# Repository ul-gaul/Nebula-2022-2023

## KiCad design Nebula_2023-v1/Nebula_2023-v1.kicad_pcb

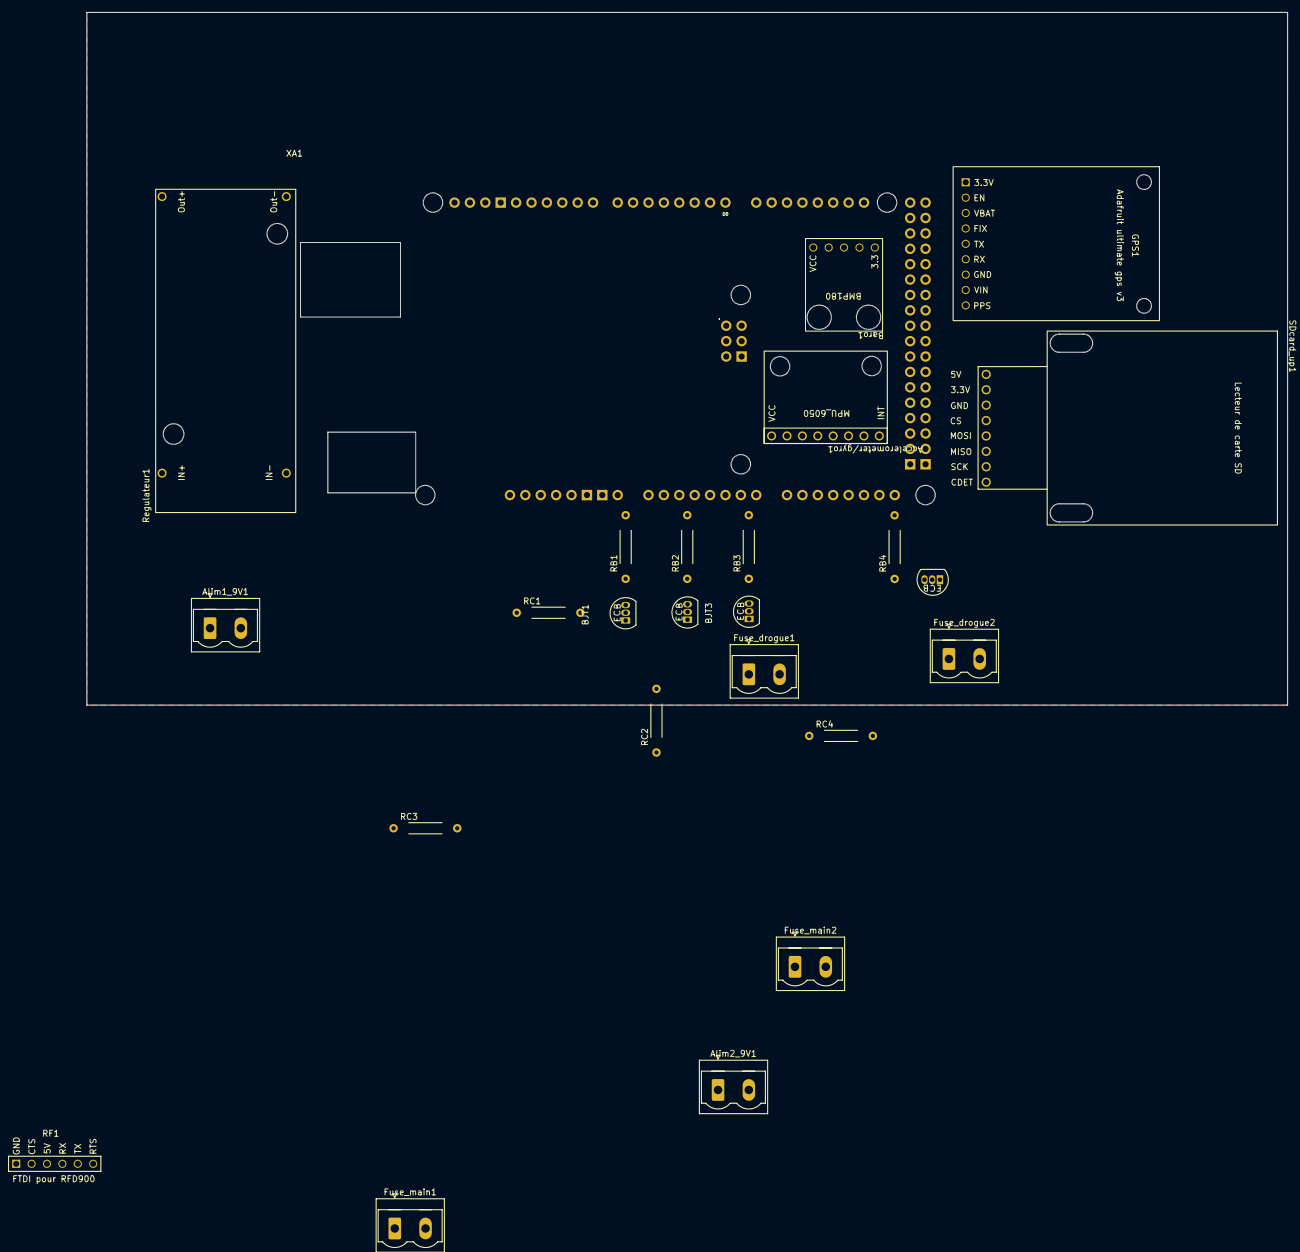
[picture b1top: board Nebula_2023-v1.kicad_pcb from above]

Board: 2 copper layers, 198.1 x 114.3 mm, 25 parts (0 on the bottom side), 34 nets, no tracks yet.

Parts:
Accelerometer/gyro1: MPU6050_6DOF_GY-521; MPU_6050
Alim1_9V1, Alim2_9V1: Screw_Terminal_KF301-2P; MKDSN_1729128_PCB terminal block
BJT1, BJT2, BJT3, BJT4: 2SC3279
Baro1: BMP18; BMP
Fuse_drogue1, Fuse_drogue2: Screw_Terminal_KF301-2P; MKDSN_1729128_PCB terminal block
Fuse_main1, Fuse_main2: Screw_Terminal_KF301-2P; MKDSN_1729128_PCB terminal block
GPS1: Adafruit_ultimate_gps_V3; Adafruit_GPS_V3
RB1, RB2, RB3, RB4: Resistance; Resistance through-hole
RC1, RC2, RC3, RC4: Resistance; Resistance through-hole
RF1: RFD900; RFD900_externe
Regulateur1: Voltage_regulator; Regulateur_voltage
SDcard_up1: Module_GPS_Robotdyn; SD Card Reader
XA1: Arduino_Mega2560_Shield; Arduino_mega_custom_shield_open

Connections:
/A1: RB1.2, XA1.A1
/A2: RB2.2, XA1.A2
/A3: RB3.2, XA1.A3
/A4: RB4.2, XA1.A4
/D2: Accelerometer/gyro1.8 (INT), XA1.D2 (D2_INT0)
/D23: GPS1.4 (FIX), XA1.D23
/D25: GPS1.9 (PPS), XA1.D25
/D50: SDcard_up1.6 (MISO), XA1.D50 (D50_MISO)
/D51: SDcard_up1.5 (MOSI), XA1.D51 (D51_MOSI)
/D52: SDcard_up1.7 (SCK), XA1.D52 (D52_SCK)
/D53: SDcard_up1.4 (CS), XA1.D53 (D53_CS)
/RX0: RF1.5 (TX), XA1.D0 (D0/RX0)
/RX1: GPS1.5 (TX), XA1.D19 (D19/RX1)
/SCL: Accelerometer/gyro1.3 (SCL), Baro1.3 (SCL), XA1.D21 (D21/SCL)
/SDA: Accelerometer/gyro1.4 (SDA), Baro1.4 (SDA), XA1.D20 (D20/SDA)
/TX0: RF1.4 (RX), XA1.D1 (D1/TX0)
/TX1: GPS1.6 (RX), XA1.D18 (D18/TX1)
/VBat1: Alim1_9V1.1 (V+), RC1.1, RC3.1, XA1.VIN
/VBat2: Alim2_9V1.1 (V+), RC2.1, RC4.1, Regulateur1.1 (IN+)
/VCC: Accelerometer/gyro1.1 (VCC), Baro1.1 (VCC), GPS1.8 (VIN), SDcard_up1.1 (5V), XA1.5V1 (5V)
/VREG_5V: RF1.3 (VCC), Regulateur1.3 (OUT+)
GND: Accelerometer/gyro1.2 (GND), Alim1_9V1.2 (V-), Alim2_9V1.2 (V-), Baro1.2 (GND), Fuse_drogue1.2 (V-), Fuse_drogue2.2 (V-), Fuse_main1.2 (V-), Fuse_main2.2 (V-), GPS1.7 (GND), Regulateur1.2 (IN-), Regulateur1.4 (OUT-), SDcard_up1.3 (GND), XA1.GND1 (GND)
unnamed: BJT1.1 (C), RC1.2
unnamed: BJT1.2 (B), RB1.1
unnamed: BJT1.3 (E), Fuse_main1.1 (V+)
unnamed: BJT2.1 (C), RC2.2
unnamed: BJT2.2 (B), RB2.1
unnamed: BJT2.3 (E), Fuse_main2.1 (V+)
unnamed: BJT3.1 (C), RC3.2
unnamed: BJT3.2 (B), RB3.1
unnamed: BJT3.3 (E), Fuse_drogue1.1 (V+)
unnamed: BJT4.1 (C), RC4.2
unnamed: BJT4.2 (B), RB4.1
unnamed: BJT4.3 (E), Fuse_drogue2.1 (V+)

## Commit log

2023-06-08 Arduino Sensors Short Code
2023-06-08 Simple example of using sensor Together with an Arrduino Mega 2560
2023-06-13 New Sensor Added
2023-06-14 testing yaw with MPU6050
2023-06-14 BNO055
2023-06-15 Just commit
2023-07-11 Firmware
2023-07-25 Test RFD900
    Create a link between 2 RFD and check if the packet is good with CRC16 (algo is MODBUS)
2023-07-26 Rename Readme to README.md
2023-08-23 Update code_fusee.ino
    add fix indicator and minor bug correction
2023-08-23 Update ground_station.ino
    Change the timeout limit from 5000 to 500
2023-09-05 [WIP]new main bord
    nouveau "croquis" main board non complété.
2023-09-05 [WIP] new main board
    croquis d'un nouveau board (non complete)
2023-09-10 Add files via upload
    The schematic is almost done
2023-09-24 Create Documentation
